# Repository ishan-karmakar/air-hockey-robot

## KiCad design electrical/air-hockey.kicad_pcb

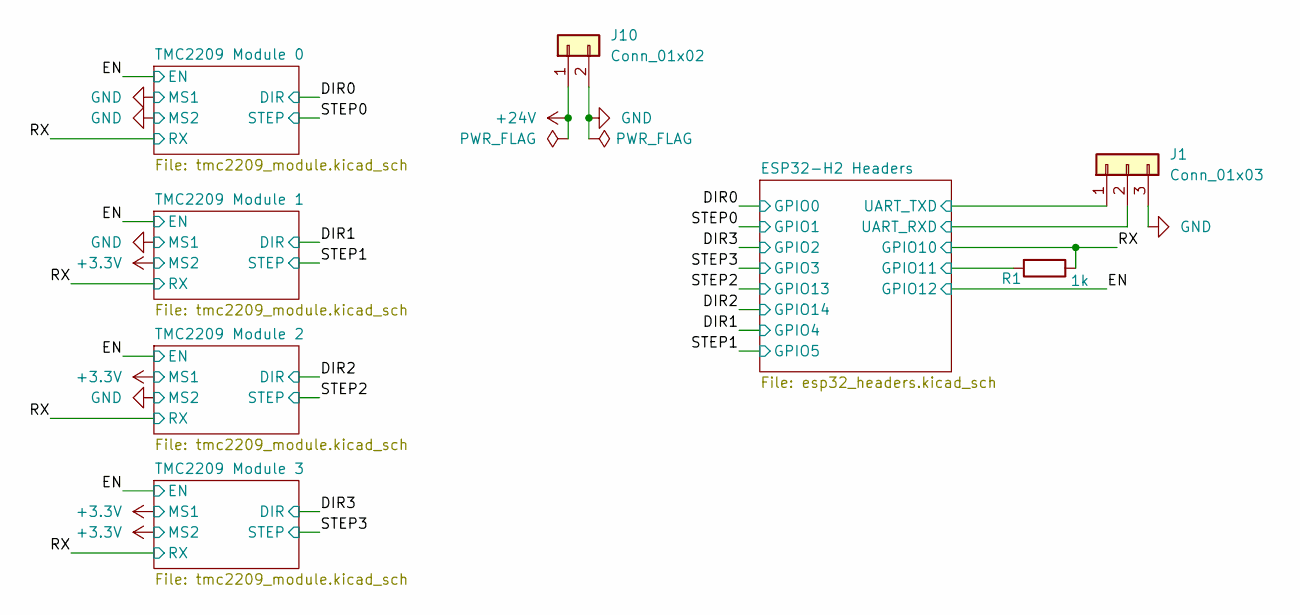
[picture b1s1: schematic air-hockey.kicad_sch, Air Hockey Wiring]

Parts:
J1: Conn_01x03; PinHeader_1x03_P2.54mm_Vertical_SMD_Pin1Left; LCSC Part # C17702634
J10: Conn_01x02; 2 Alligator Clip Holes
R1: 1k; R_0603_1608Metric; LCSC Part # C21190

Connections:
+24V: J10.1; also elsewhere on the board
/ESP32-H2 Headers/GPIO11: R1.2; also elsewhere on the board
/ESP32-H2 Headers/UART_RXD: J1.2; also elsewhere on the board
/ESP32-H2 Headers/UART_TXD: J1.1; also elsewhere on the board
/RX: R1.1; also elsewhere on the board
GND: J1.3, J10.2; also elsewhere on the board

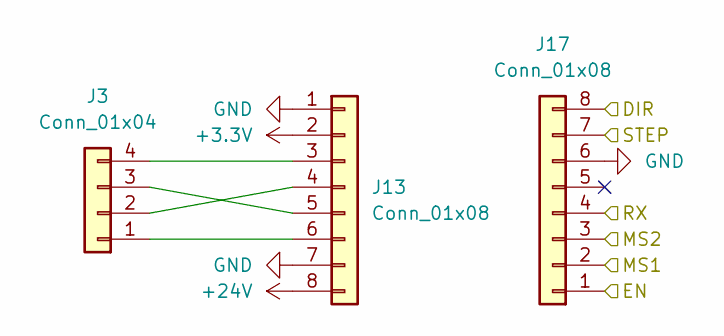
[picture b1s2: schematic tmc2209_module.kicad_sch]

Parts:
J3: Conn_01x04; PinHeader_1x04_P2.54mm_Vertical_SMD_Pin1Left; LCSC Part # C5160787
J13, J17: Conn_01x08; PinSocket_1x08_P2.54mm_Vertical; LCSC Part # C429957

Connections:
+3.3V: J13.2; also elsewhere on the board
+24V: J13.8; also elsewhere on the board
/DIR0: J17.8; also elsewhere on the board
/EN: J17.1; also elsewhere on the board
/RX: J17.4; also elsewhere on the board
/STEP0: J17.7; also elsewhere on the board
GND: J13.1, J13.7, J17.2, J17.3, J17.6; also elsewhere on the board
unnamed: J3.4, J13.3
unnamed: J3.2, J13.4
unnamed: J3.3, J13.5
unnamed: J3.1, J13.6

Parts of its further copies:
J7, J8, J9: Conn_01x04; PinHeader_1x04_P2.54mm_Vertical_SMD_Pin1Left; LCSC Part # C5160787
J14, J15, J16, J18, J19, J20: Conn_01x08; PinSocket_1x08_P2.54mm_Vertical; LCSC Part # C429957

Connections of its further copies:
+3.3V: J14.2, J15.2, J16.2, J18.3, J19.2, J20.2, J20.3; also elsewhere on the board
+24V: J14.8, J15.8, J16.8; also elsewhere on the board
/DIR1: J18.8; also elsewhere on the board
/DIR2: J19.8; also elsewhere on the board
/DIR3: J20.8; also elsewhere on the board
/EN: J18.1, J19.1, J20.1; also elsewhere on the board
/RX: J18.4, J19.4, J20.4; also elsewhere on the board
/STEP1: J18.7; also elsewhere on the board
/STEP2: J19.7; also elsewhere on the board
/STEP3: J20.7; also elsewhere on the board
GND: J14.1, J14.7, J15.1, J15.7, J16.1, J16.7, J18.2, J18.6, J19.3, J19.6, J20.6; also elsewhere on the board
unnamed: J7.4, J14.3
unnamed: J7.2, J14.4
unnamed: J7.3, J14.5
unnamed: J7.1, J14.6
unnamed: J8.4, J15.3
unnamed: J8.2, J15.4
unnamed: J8.3, J15.5
unnamed: J8.1, J15.6
unnamed: J9.4, J16.3
unnamed: J9.2, J16.4
unnamed: J9.3, J16.5
unnamed: J9.1, J16.6

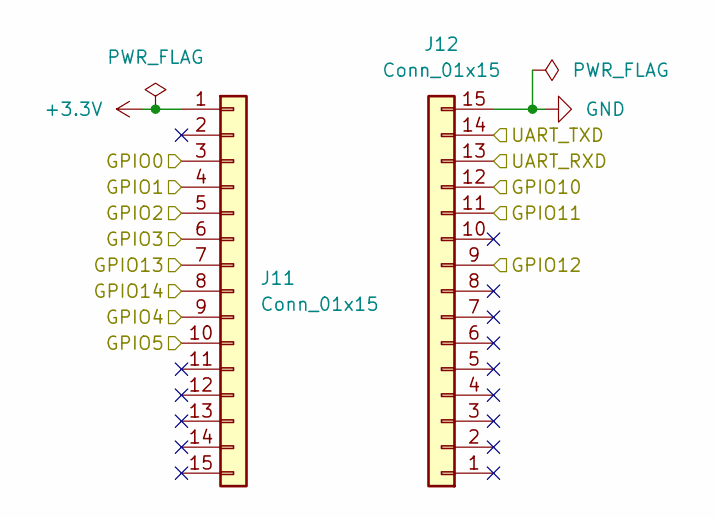
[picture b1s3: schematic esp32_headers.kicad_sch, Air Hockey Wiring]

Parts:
J11, J12: Conn_01x15; PinSocket_1x15_P2.54mm_Vertical; LCSC Part # C25503121

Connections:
+3.3V: J11.1; also elsewhere on the board
/DIR0: J11.3; also elsewhere on the board
/DIR1: J11.9; also elsewhere on the board
/DIR2: J11.8; also elsewhere on the board
/DIR3: J11.5; also elsewhere on the board
/EN: J12.9; also elsewhere on the board
/ESP32-H2 Headers/GPIO11: J12.11; also elsewhere on the board
/ESP32-H2 Headers/UART_RXD: J12.13; also elsewhere on the board
/ESP32-H2 Headers/UART_TXD: J12.14; also elsewhere on the board
/RX: J12.12; also elsewhere on the board
/STEP0: J11.4; also elsewhere on the board
/STEP1: J11.10; also elsewhere on the board
/STEP2: J11.7; also elsewhere on the board
/STEP3: J11.6; also elsewhere on the board
GND: J12.15; also elsewhere on the board

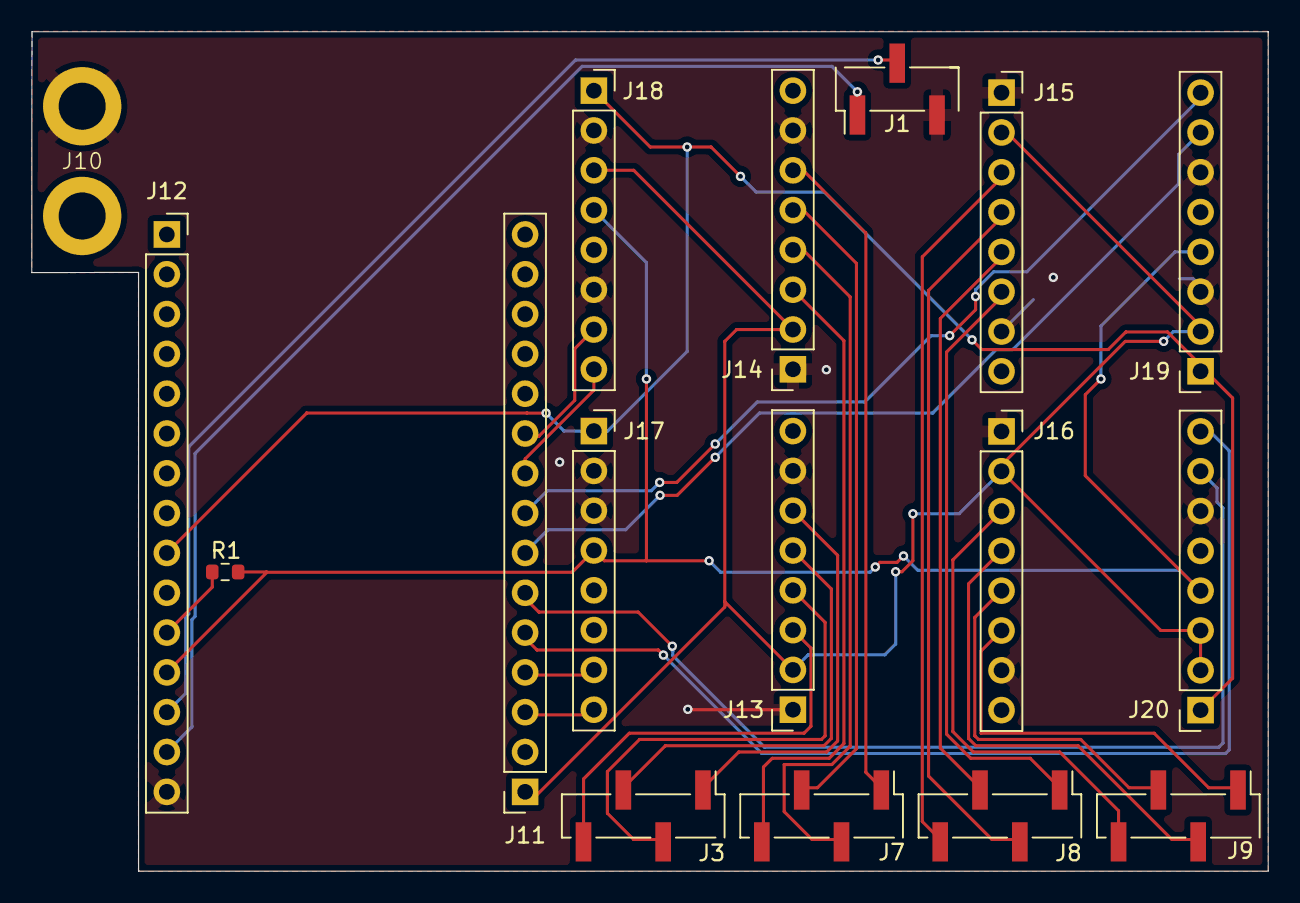
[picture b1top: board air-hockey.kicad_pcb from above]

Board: 4 copper layers, 78.9 x 53.6 mm, 17 parts (0 on the bottom side), 32 nets.
